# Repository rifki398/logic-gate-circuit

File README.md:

# Logic Gate Circuit
<table>
  <tr>
    <td align="center">
      
      <br/>3D View
    </td>
    <td align="center">
      
      <br/>Board View
    </td>
  </tr>
</table>

## Description
This project is a PCB design created with KiCad for simulating and testing basic logic gates: OR, AND, NOT, NOR, NAND, XOR, and XNOR. It is intended for educational purposes, allowing students or hobbyists to easily visualize and experiment with digital logic circuits. The board uses a LM7805 voltage regulator to provide a stable +5 V supply, 2N2222 transistors for logic gate implementation, push buttons as input switches, and resistors for biasing and pull-up/pull-down configurations.

## Bill of Materials (BOM)
| No. | Component                     | Quantity | Description / Value           | Package Type |
|-----|--------------------------------|----------|--------------------------------|--------------|
| 1   | LM7805 Voltage Regulator       | 1        | +5 V output, 1 A               | TO-220       |
| 2   | 2N2222 NPN Transistor          | 18       | For each logic gate output     | TO-92        |
| 3   | Push Button Switch             | 13        | Logic gate input control       | 2 pin 6x6x5 |
| 4   | Barrel Jack Connector          | 1        | DC input, 5–12 V               | THT          |
| 5   | LED Indicator                  | 7        | Logic output visualization     | 5 mm THT     |
| 6   | Capacitor (Electrolytic)       | 2        | 10 µF, for voltage smoothing   | Radial THT   |
| 7   | Resistor                       | Various  | Biasing & pull-up/pull-down    | Axial THT    |

For resistor specification, please check the schematic or board.

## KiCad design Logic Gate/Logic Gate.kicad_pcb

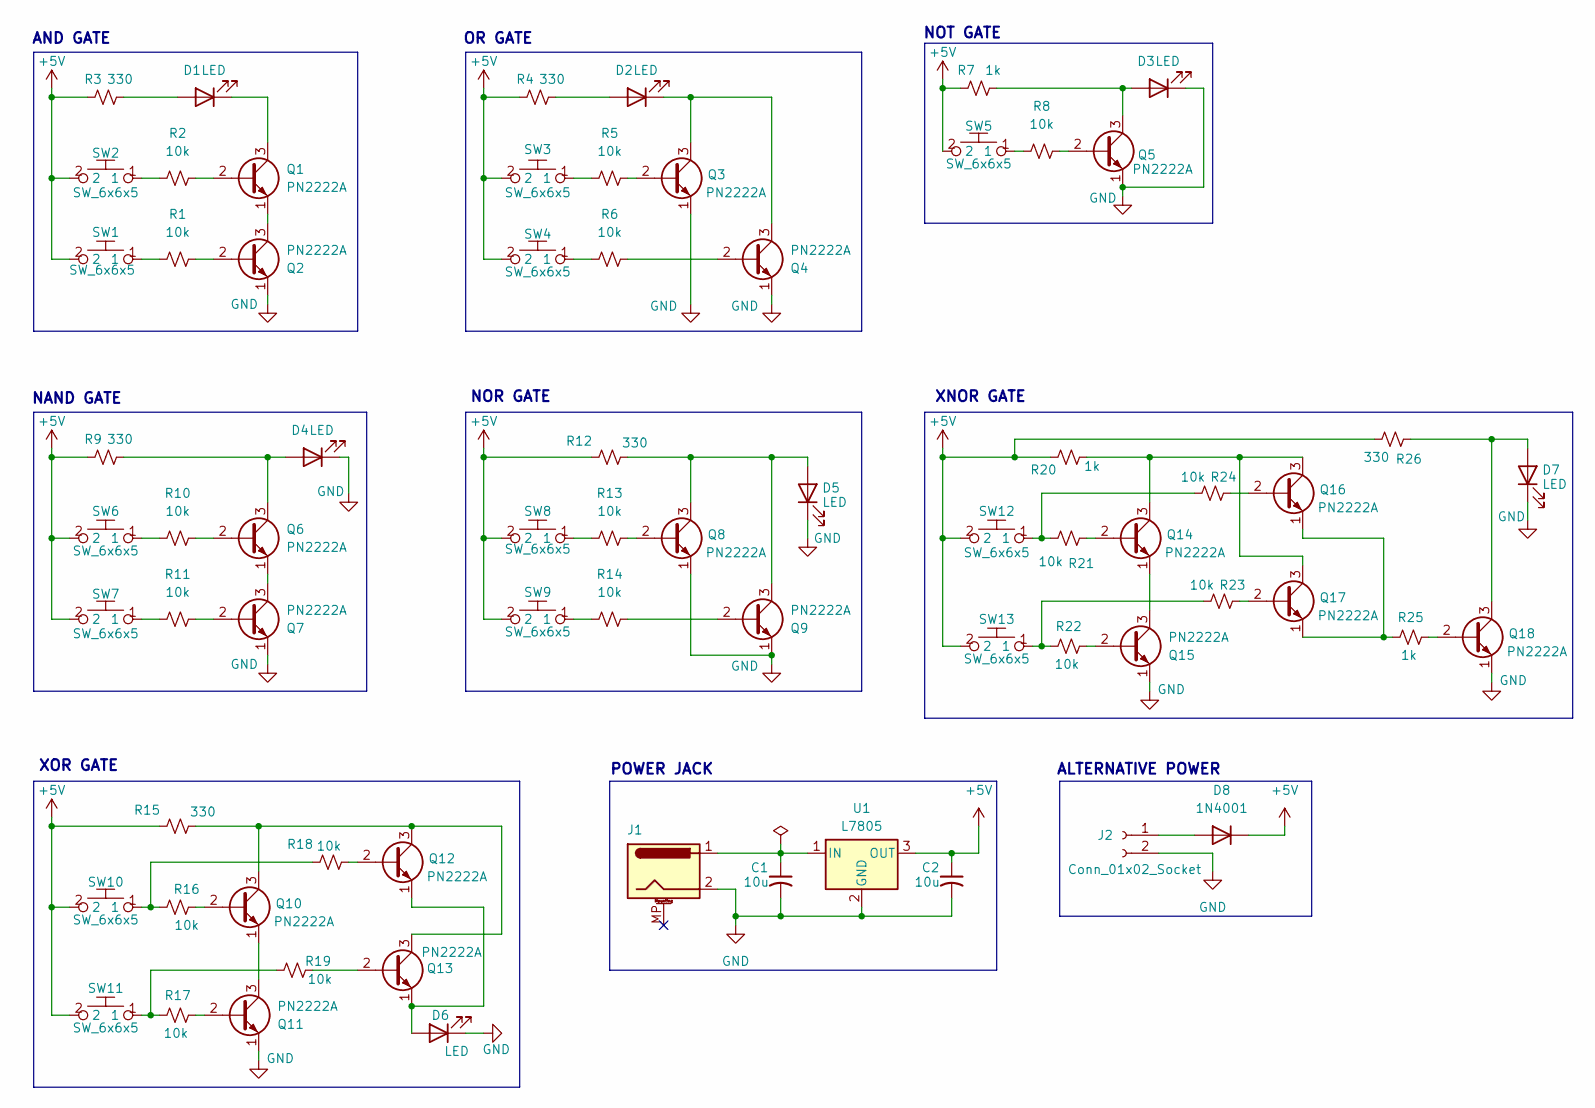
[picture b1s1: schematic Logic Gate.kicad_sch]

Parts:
C1, C2: 10u; C_Radial_D5.0mm_H11.0mm_P2.00mm
D1, D2, D3, D4, D5, D6, D7: LED; LED_D5.0mm_IRBlack
D8: 1N4001; D_DO-41_SOD81_P10.16mm_Horizontal
J1: Barrel_Jack_MountingPin; BarrelJack_Horizontal
J2: Conn_01x02_Socket; PinSocket_1x02_P2.54mm_Vertical
Q1, Q2, Q3, Q4, Q5, Q6, Q7, Q8, Q9, Q10, Q11, Q12, Q13, Q14, Q15, Q16, Q17, Q18: PN2222A; TO-92_Inline
R1, R2, R5, R6, R8, R10, R11, R13, R14, R16, R17, R18, R19, R21, R22, R23, R24: 10k; R_Axial_DIN0309_L9.0mm_D3.2mm_P12.70mm_Horizontal
R3, R4, R9, R12, R15, R26: 330; R_Axial_DIN0309_L9.0mm_D3.2mm_P12.70mm_Horizontal
R7, R20, R25: 1k; R_Axial_DIN0309_L9.0mm_D3.2mm_P12.70mm_Horizontal
SW1, SW2, SW3, SW4, SW5, SW6, SW7, SW8, SW9, SW10, SW11, SW12, SW13: SW_6x6x5; Btn_6x6x5
U1: L7805; TO-220-3_Vertical

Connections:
+5V: C2.1, D8.1 (K), R3.2, R4.2, R7.2, R9.2, R12.2, R15.2, R20.2, R26.1, SW1.2, SW2.2, SW3.2, SW4.2, SW5.2, SW6.2, SW7.2, SW8.2, SW9.2, SW10.2, SW11.2, SW12.2, SW13.2, U1.3 (OUT)
GND: C1.2, C2.2, D3.1 (K), D4.1 (K), D5.1 (K), D6.1 (K), D7.1 (K), J1.2, J2.2, Q2.1 (E), Q3.1 (E), Q4.1 (E), Q5.1 (E), Q7.1 (E), Q8.1 (E), Q9.1 (E), Q11.1 (E), Q15.1 (E), Q18.1 (E), U1.2 (GND)
unnamed: D1.2 (A), R3.1
unnamed: D1.1 (K), Q1.3 (C)
unnamed: D2.2 (A), R4.1
unnamed: D2.1 (K), Q3.3 (C), Q4.3 (C)
unnamed: D3.2 (A), Q5.3 (C), R7.1
unnamed: D4.2 (A), Q6.3 (C), R9.1
unnamed: D5.2 (A), Q8.3 (C), Q9.3 (C), R12.1
unnamed: D6.2 (A), Q12.1 (E), Q13.1 (E)
unnamed: D7.2 (A), Q18.3 (C), R26.2
unnamed: D8.2 (A), J2.1
unnamed: Q1.2 (B), R2.2
unnamed: Q1.1 (E), Q2.3 (C)
unnamed: Q2.2 (B), R1.2
unnamed: Q3.2 (B), R5.2
unnamed: Q4.2 (B), R6.2
unnamed: Q5.2 (B), R8.2
unnamed: Q6.2 (B), R10.2
unnamed: Q6.1 (E), Q7.3 (C)
unnamed: Q7.2 (B), R11.2
unnamed: Q8.2 (B), R13.2
unnamed: Q9.2 (B), R14.2
unnamed: Q10.2 (B), R16.2
unnamed: Q10.3 (C), Q12.3 (C), Q13.3 (C), R15.1
unnamed: Q10.1 (E), Q11.3 (C)
unnamed: Q11.2 (B), R17.2
unnamed: Q12.2 (B), R18.2
unnamed: Q13.2 (B), R19.2
unnamed: Q14.2 (B), R21.2
unnamed: Q14.3 (C), Q16.3 (C), Q17.3 (C), R20.1
unnamed: Q14.1 (E), Q15.3 (C)
unnamed: Q15.2 (B), R22.2
unnamed: Q16.2 (B), R24.2
unnamed: Q16.1 (E), Q17.1 (E), R25.1
unnamed: Q17.2 (B), R23.2
unnamed: Q18.2 (B), R25.2
unnamed: R1.1, SW1.1
unnamed: R2.1, SW2.1
unnamed: R5.1, SW3.1
unnamed: R6.1, SW4.1
unnamed: R8.1, SW5.1
unnamed: R10.1, SW6.1
unnamed: R11.1, SW7.1
unnamed: R13.1, SW8.1
unnamed: R14.1, SW9.1
unnamed: R16.1, R18.1, SW10.1
unnamed: R17.1, R19.1, SW11.1
unnamed: R21.1, R24.1, SW12.1
unnamed: R22.1, R23.1, SW13.1
unnamed: C1.1, J1.1, U1.1 (IN)

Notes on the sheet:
NOT GATE
NOR GATE
POWER JACK
OR GATE
NAND GATE
AND GATE
ALTERNATIVE POWER
XNOR GATE
XOR GATE

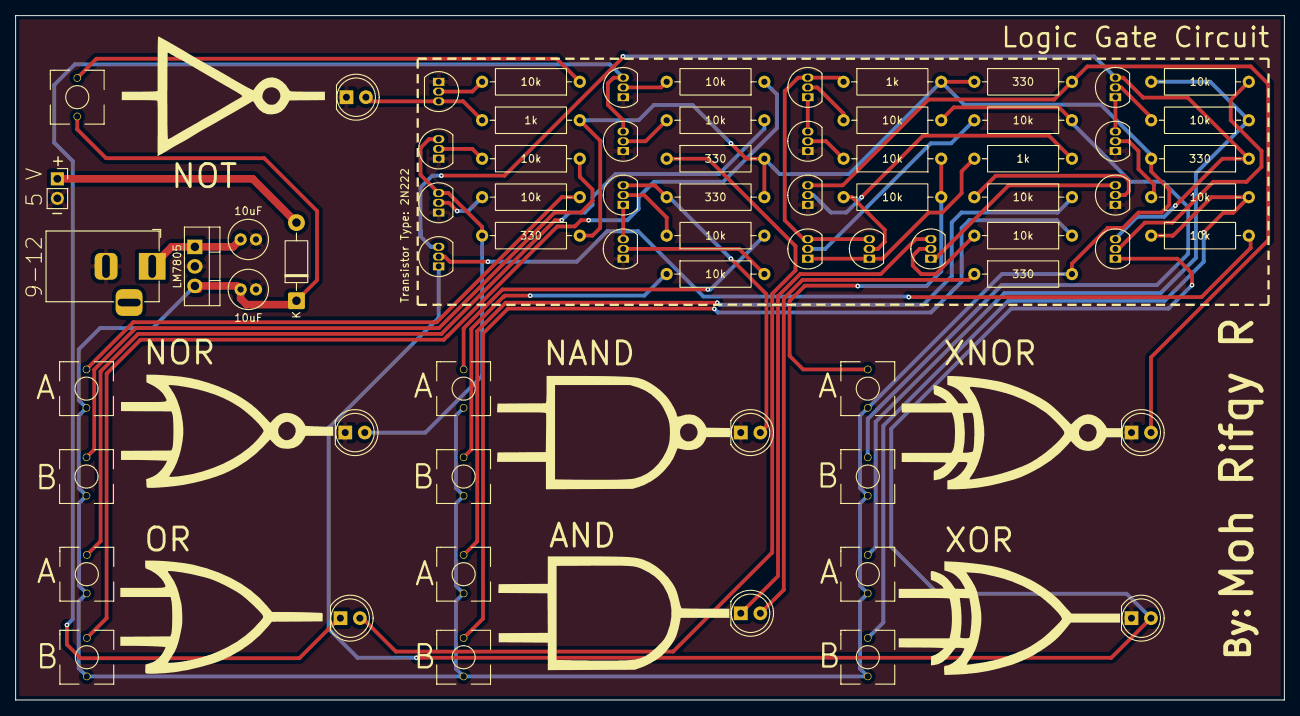
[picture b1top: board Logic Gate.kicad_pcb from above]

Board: 2 copper layers, 165.0 x 89.0 mm, 70 parts (0 on the bottom side), 51 nets.

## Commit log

2025-08-18 Traces revision
2025-08-23 minimum size
2025-08-28 Backup
